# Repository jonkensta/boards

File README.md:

# boards

KiCad PCB projects plus the tooling to scaffold, check, and export them.
Requires KiCad 10 (`kicad-cli` on `PATH`), GNU make, Python 3, bash, and `unzip`.
No KiCad Python bindings are used anywhere (see "Design" below).

## Layout

```
boards/<id>/            one KiCad project per board, any depth; files named after the leaf dir
                        (boards/blinky/blinky.kicad_pro, boards/chromatone/isolator/isolator.kicad_pro)
lib/                    shared symbols, footprints, 3D models (nickname `boards` in every project)
templates/board/        project template used by `make new`
jobsets/fab.kicad_jobset  the one definition of every fabrication export (GUI and CLI)
boardtools/             Python helpers: s-expr parser, board facts, JLCPCB conversion, Specctra
                        DSN/SES, and the schematic/board generators (schgen, pcbgen) used by
                        boards/*/generate/
scripts/                scaffolder, smoke test, Freerouting autorouter (route.py)
boards/<id>/out/        generated outputs (git-ignored)
.github/workflows/      CI: unit tests, smoke test, ERC/DRC, fab exports in kicad/kicad:10.0
```

## Boards

| Board | What | Status (2026-09-19) |
| --- | --- | --- |
| [`chromatone/isolator`](boards/chromatone/isolator/README.md) | ISO7720 isolated SPI daughterboard, Pi (3.3 V) -> SK9822 strip (5 V), 46 x 30 mm | Rev A layout done, review-clean; pick passives in JLCPCB's BOM tool, then orderable |
| [`chromatone/dac`](boards/chromatone/dac/README.md) | PCM5102A I2S line-out DAC (experiment), 56 x 36 mm | Rev A layout done, review-clean, fully numbered BOM; not yet built |
| [`net/node`](boards/net/node/README.md) | RP2040 sensor-net node with neighbour links, four corner LEDs and sensor build variants, 48 x 48 mm, 4 layers | Rev A layout done and reviewed; ready to order after the owner's GUI check and quote (see its Resume path); no firmware yet |

`boards/chromatone/README.md` holds the Chromatone-wide decisions, strip wiring, order and
bench checklists. Every board so far was generated from `generate/` scripts (see below) and
put through an adversarial Codex review loop before being called done.

## Usage

```sh
make new NAME=blinky        # scaffold boards/blinky (fresh UUIDs, 50×50 mm outline, lib tables wired to lib/)
make new NAME=proj/rev2     # nested ids work too: boards/proj/rev2/rev2.kicad_pro
kicad boards/blinky/blinky.kicad_pro

make check  BOARD=blinky    # off-grid lint + ERC + DRC (schematic parity, zones refilled); fails on errors (STRICT=1: also warnings)
make fab    BOARD=blinky    # check, then run jobsets/fab.kicad_jobset -> boards/blinky/out/
make jlcpcb BOARD=blinky    # fab, then JLCPCB-format BOM + CPL -> boards/blinky/out/jlcpcb/
make parts  BOARD=blinky    # after fab: check every LCSC number in the BOM against JLCPCB's catalog
make check                  # all boards
make fab                    # all boards
make route  BOARD=blinky    # autoroute a placed board with Freerouting -> boards/blinky/out/route/ (see below)
```

`make fab` produces, per board (paths below are inside `boards/<id>/out/`):

| Output | Path |
| --- | --- |
| ERC/DRC reports (gating violations, plus a separate warnings report) | `{erc,drc}.rpt`, `{erc,drc}-warnings.rpt` |
| Off-grid connection points (gating; see `boardtools offgrid`) | `offgrid.rpt` |
| Gerbers (all copper layers up to In30, paste, silk, mask, edge) + `.gbrjob` | `./` |
| Excellon drill (PTH/NPTH split) + Gerber X2 maps | `drill/` |
| Gerbers + drill zipped for fab upload (no drill maps) | `<leaf>-gerbers.zip` |
| Pick-and-place CSV (mm, drill origin, DNP excluded) | `<leaf>-all-pos.csv` |
| BOM CSV grouped by Value/Description/Footprint/MPN/Manufacturer/LCSC | `<leaf>-bom.csv` |
| Schematic PDF | `<leaf>-schematic.pdf` |
| STEP model | `<leaf>.step` |
| JLCPCB CPL + BOM (`make jlcpcb`) | `jlcpcb/` |

The same jobset runs from the KiCad project manager: Jobsets → open `jobsets/fab.kicad_jobset`
→ run. Change export settings there once and both GUI and CI follow.

Other targets: `make parts` (see boardtools below), `make export` (jobset without the Makefile checks), `make erc|drc`, `make test`
(boardtools unit tests), `make smoke` (scaffolds throwaway 2- and 8-layer boards in a temp dir
and runs the whole pipeline, including a deliberate DRC failure and an off-grid child-sheet item), `make list`,
`make clean`.

KiCad 10 **design variants** (per-symbol DNP/field overrides, used by `net/node`) are honoured
by `kicad-cli sch export bom --variant <name>` and `pcb export pos --variant <name>`; the
jobset and `make jlcpcb` export the default variant only (backlog item 9 in `CLAUDE.md`).

## boardtools

```sh
python3 -m boardtools layers boards/blinky/blinky.kicad_pcb   # F.Cu,In1.Cu,In2.Cu,B.Cu
python3 -m boardtools info   boards/blinky/blinky.kicad_pcb   # title block + layer count
python3 -m boardtools jlcpcb pos <kicad-pos.csv> <cpl.csv>
python3 -m boardtools jlcpcb bom <kicad-bom.csv> <jlc-bom.csv>   # warns on lines without LCSC
python3 -m boardtools parts <kicad-bom.csv> [--db PATH] [--boards N] [--strict]
python3 -m boardtools offgrid boards/blinky/blinky.kicad_sch [--grid 1.27]
```

`parts` (and `make parts`, which checks the BOM `make fab` left in `out/` and refuses if it
is missing or older than the schematics, project file or jobset) is a **manual pre-order check**, not part of CI, because it
needs the network and uses the undocumented search endpoint behind jlcpcb.com/parts (one
request per distinct LCSC number, four at a time), which JLCPCB may change without notice.
`--db PATH` queries a jlcparts-style SQLite snapshot offline instead. It prints one row per
BOM line with basic/preferred/extended, live stock, and any problems:

- error: LCSC number malformed, not found at JLCPCB, or lookup failed (network/HTTP).
  With `--db` a miss is only "not in snapshot": snapshots omit parts with fewer than 5 in
  stock, and one with far fewer than ~600k parts is flagged as partial.
- warning: no LCSC number (nothing marks a line as hand-assembled, so this may be deliberate),
  stock below or within 3x of Qty x `--boards` (default 5, summed per LCSC number), MPN differs
  from the catalog, chip size in the footprint (0402/0603/...) differs from the catalog package.
- the summary counts distinct extended parts, each of which costs JLCPCB's loading fee.

Exit 1 on errors (`--strict` or `make parts STRICT=1`: also warnings), 2 if every lookup
failed or `--db` is unusable. Extra options go through `PARTS_ARGS`, e.g. `make parts PARTS_ARGS='--boards 10'`.

`offgrid` lists every electrical connection point off the 1.27 mm grid (symbol pins computed
from the embedded library symbols with the instance's rotation/mirror/unit/body style, wire
and bus ends, bus entries, junctions, no-connects, labels, sheet pins) in the sheet and every
child sheet file, one line per item with the sheet file and the nearest grid point, and exits 1
if there are any. `erc/<id>` gates on it as well as on ERC (both always run, so every report is
fresh): KiCad's ERC only warns (`endpoint_off_grid`) and reports one pin per symbol. `Schematic.write()`
in schgen refuses to write an off-grid sheet.

## Generating boards from Python

`boardtools.schgen` and `boardtools.pcbgen` write native `.kicad_sch` / `.kicad_pcb` files from
short Python scripts using the stock symbol and footprint libraries. `boards/*/*/generate/`
show the pattern: place symbols on the 1.27 mm grid, draw wires (or local labels for big parts),
run ERC, export the netlist, place footprints, route with `N(ref, pin)` net lookups, pour, run
DRC with `--refill-zones --save-board`, render. No KiCad Python bindings are involved.
Regenerating replaces every UUID, so once a board is edited in the KiCad GUI the scripts become
history rather than the source. `CLAUDE.md` lists the format details that cost time to learn
(pin transforms, junctions, PWR_FLAG, 0.65 mm pitch fan-out, mirrored silk, keepouts).

## Autorouting (Freerouting)

For a board whose placement is done, `make route BOARD=<id>` autoroutes it with
[Freerouting](https://github.com/freerouting/freerouting) and DRCs the result:

```sh
make route BOARD=chromatone/isolator                     # keep existing tracks/vias, route the rest
make route BOARD=chromatone/isolator ROUTE_ARGS=--strip  # drop all tracks/vias first, route from scratch
PASSES=20 make route BOARD=...                           # cap Freerouting's passes (default 100)
```

It writes a **new** board, `boards/<id>/out/route/<leaf>.kicad_pcb` (next to copies of the
project, rules and schematic so parity DRC works there, plus the `.dsn`, `.ses`,
`freerouting.log` and `drc.rpt`), then runs the same strict DRC as `make check` with
`--save-board` so the copy has its zones filled. The source board is never touched: open the
routed copy in KiCad, review it, and copy it over `boards/<id>/<leaf>.kicad_pcb` by hand if you
keep it. The default output directory `out/route/` is the only thing the script ever deletes:
it checks that `out/` and `out/route/` are real directories, then removes and recreates
`out/route/`, so no planted symlink or hard link can redirect any write (including DRC's
report) onto a source file. `scripts/route.py -o DIR` takes a new or empty real directory
only, never clears it, and refuses one that contains the board or lies inside the board's
directory other than under `out/`. `make fab`/`make clean` delete `out/`, including this.

kicad-cli has no Specctra DSN export or SES import (only the pcbnew GUI and its SWIG bindings
do), so `boardtools/specctra.py` writes the DSN and reads the SES textually, and
`scripts/route.py` appends the session's new tracks and vias to a copy of the board.
Freerouting runs from the Docker image `ghcr.io/freerouting/freerouting:2.4.1` (the release
jar needs Java 25); set `FREEROUTING="java -jar /path/to/freerouting-2.4.1.jar"` to use a
local jar, `FREEROUTING_VERSION` to pick another image tag. It is not part of CI or smoke.

What goes into the DSN: copper layers, the Edge.Cuts outline (inner loops as cut-outs), every
pad with its real shape and rotation on either side (rect, roundrect, oval, circle; chamfered
pads as their rectangle; trapezoid and custom pads as a rectangle enclosing all their copper,
primitives and strokes included), SMD and THT, NPTH holes and slots (slot walls also get the
copper-to-edge clearance, as KiCad's DRC applies it),
rule-area keepouts on the board and inside footprints, copper pours as planes (zone holes as
windows), existing tracks and vias as protected wiring, and netclass track width / clearance /
via size from the `.kicad_pro` (patterns and explicit assignments; a net in several classes
takes each rule from the highest-priority class that sets it, as KiCad 10 does). Net, reference
and pin names that a DSN cannot carry (`"`, backslash, non-ASCII) get generated identifiers and
are mapped back on import. Not modelled: per-layer padstacks, blind/buried/micro vias, arcs
(existing ones go in as chords), `.kicad_dru` custom rules, length/differential-pair
constraints. Tracks get their netclass width, so give power nets a
netclass if they need to be wider than Default. The router knows nothing about analog
return paths or decoupling loops; route those by hand first and let it finish the rest.

Verified on `chromatone/isolator` and `chromatone/dac` with all routing stripped: 100 %
routed in 4 to 10 s, 0 DRC errors, 0 warnings, 0 unconnected, 0 parity issues. Also clean:
the isolator with R1 (30 deg) and U1 (90 deg) moved to the back, and with a quoted net name
and a hole in a ground pour.

## Review workflow

Tooling changes and boards are reviewed adversarially with the Codex CLI: one fresh
`codex exec -s read-only` review, then `codex exec resume --last` rounds after each fix until
it reports no substantive findings. Codex is asked to reproduce (run `make test`/`make smoke`,
scaffold boards, run DRC in a temp copy), not just read. The findings that changed the design
are summarised in `CLAUDE.md` under "Review history".

## Design

- **Exports live in the jobset, checks live in the Makefile.** KiCad jobsets are the native,
  declarative way to define outputs and `kicad-cli jobset run` executes them headlessly. The
  Makefile adds what jobsets cannot: a separate warnings report, `STRICT`, purging stale outputs,
  and a hard guarantee that ERC/DRC pass before anything is exported (inside a jobset, a failing
  job only stops its own destination, and only with `--stop-on-error`).
- **No KiCad Python bindings.** The SWIG `pcbnew` module is deprecated and removed in KiCad 11;
  the IPC API needs a running KiCad and cannot export before KiCad 11. `boardtools` therefore
  only parses files (s-expressions, JSON, CSV). Anything that must modify a design goes through
  `kicad-cli` or the jobset. The one exception is `scripts/route.py`, which appends
  autorouted tracks to a *copy* of a board, because kicad-cli cannot import a Specctra session.
- **Template rules are conservative** (0.15 mm track/clearance, 0.3 mm drill, 0.3 mm copper-to-edge).
  Tighten or loosen per board in Board Setup → Constraints to match the fab.

## Conventions

- Put `MPN`, `Manufacturer`, and (for JLCPCB assembly) `LCSC` fields on symbols; the BOM export
  and JLCPCB conversion use them. Put ratings (dielectric, voltage, tolerance) in `Description`;
  it is exported and appended to the JLCPCB Comment.
- Custom parts go in `lib/`; stock KiCad library parts are referenced as usual.
- The template sets the drill/place origin at the outline's bottom-left corner; move it if you
  move the outline. Gerbers, drill, and position files use it.
- Board revision lives in the schematic title block.
- JLCPCB rotations are passed through unchanged; check the placement preview on the order page.
- Mounting holes get copper keepouts (`Board.keepout`) and nylon standoffs; on isolated boards
  metal hardware would tie the domains together.
- Passive references go on `F.Fab` (hidden); silk carries connector pin labels and test-point
  names instead.

## Where things stand

- Tooling is complete for the current workflow: scaffold, check, export, JLCPCB files, CI.
- Optional Freerouting autorouting (`make route`), outside CI.
- Backlog, ranked, lives in `CLAUDE.md` ("Ideas not yet implemented"): order bundle with a
  manifest, BOM/CPL lint (catalog side done: `make parts`), per-fab constraint profiles, HTML BOM, assembly drawings and revision
  diffs, panelization, revision in PCB markings, hierarchical sheets in `schgen`, per-variant
  jobset outputs, autorouter follow-ups.
- Known gap: `pcbgen` does not yet carry a schematic DNP flag onto footprints (parity DRC only
  warns about it).

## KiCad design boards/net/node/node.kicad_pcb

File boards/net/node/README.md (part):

# net/node

One cell of a sensor "net": a small RP2040 board with four corner RGB LEDs, a sensor and four
neighbour links. A node that detects something lights up and tells its neighbours; they
repeat the excitation one level weaker, so a wave ripples outwards and dies away. Any number
of nodes are tiled and cabled edge to edge (grid, hexagonal patch, irregular drape over a bush).

## Status: rev A ready to order pending the owner's GUI look and quote; reviewed (2026-09-25)

**Where it stands (2026-09-25, commit b260c7f):** every layout change of 2026-09-24/25 passed a
reproduction-based Codex review to NO SUBSTANTIVE FINDINGS (floorplan and J5 removal, crystal
isolation, corner LEDs and the pre-order fixes). A three-model pre-order panel (Codex, Kimi K3,
Gemini; Gemini weighted 1/4 at the owner's request) ran on 5175f76: Codex found the missing
BOOT 1 k (confirmed against the RP2040 hardware design guide p.9), hot-plug overvoltage, USB
backfeed and a piezo DC drive mode; Kimi's XSHUT claim was wrong (pads reset pulled down,
datasheet table 341). All accepted findings are fixed in b260c7f. What remains is in Resume path
items 4..7: the owner's GUI / 1:1 paper check, the quote, a small first batch, loose parts and cables.

2026-09-25: the single LED D2 (and the DNP D4) became **four WS2812B-2020-V6, one per corner** (D1..D4,
chained NE -> NW -> SW -> SE), run from +5V through a 5 V buffer U5 instead of the old D1 drop diode; the
panel's pre-order findings went in at the same time (BOOT 1 k R19, TVS D5, USB backfeed Schottky D6, balanced
quiet piezo drive, J1..J4 / SW1 out of the placement file, no vias in the J6 pogo pads). Board still 48 x 48.
`make check` 0 / 0 / 0 and no warnings, `make parts` 25 lines 0 / 0. See the Decisions entries dated
2026-09-25. The earlier status follows.

Rev A schematic is generated and ERC-clean. `generate/pcb.py` places and routes the whole
board (48 x 48 mm, 4 layers); `make check BOARD=net/node` passes with 0 violations,
0 unconnected items, 0 schematic-parity issues and no warnings. On 2026-09-24 the board was
re-placed and re-routed to the floorplan rule in Decisions: the RP2040 and its immediate
support fill the centre square between the four link housings, the peripherals take the
corners, and no pad, via, part or courtyard comes within 3.7 mm of a mounting-hole centre.
The sensor header J5 was removed in the same pass (see Decisions, sensor variants). The side-entry
connectors, their tiling alignment and the earlier review fixes are unchanged; the new layout has
not been reviewed yet (see Resume path). **No firmware, nothing ordered, no jig built.** LCSC
numbers verified 2026-09-24 via `make parts` (see Parts and cost). Next: review,
`make jlcpcb BOARD=net/node`, order-page check, jig.

## Concept and first-iteration scope

- The original idea: a cheap board with a bright LED, connected to four others, those to four
  more, forming a net that can be laid over an object, a wall or a bush. Each board has a sensor;
  on detection it lights up and signals its neighbours, who act on it with the signal
  attenuated at each hop.
- The behaviour is a cellular automaton: node state depends only on its own sensor and its
  immediate neighbours. That fact drove every interconnect decision below.
- First iteration is a **proof of concept**: indoor, no outdoor-proofing (no ESD/TVS on the
  links, no sealed connectors, no conformal coat), a **proximity** sensor first, and **per-node
  cost is the priority** because there may be many nodes. The vibration switch for a bush is
  kept as a build variant so the same PCB serves both.

## Decisions

- **Point-to-point neighbour links, not a bus.** The behaviour is local, so the cable topology
  *is* the logic topology: no addressing, no termination, no row/column config, any shape
  (irregular patches, 3- or 6-neighbour nodes, a cut net still works). The port a message
  arrives on gives direction for free (waves, flow away from source). A dead node is a hole the
  wave flows around. Rejected: CAN per row and column (two controllers and transceivers per
  node, termination at every row/column end, forces a rectangular grid, needs position config;
  contention was never the issue, a 20-node row at 500 kbit/s is idle), RS-485 (same problems),
  wireless / ESP-NOW / BLE mesh (removes data wires but not power, and adjacency from RSSI is
  unreliable; only worth it with battery nodes and much smaller LEDs).
- **Link = 5 V, DATA, GND on a keyed JST-XH 3-pin** (J1..J4 = N, E, S, W), straight cable, no
  crossover. DATA is a single-wire half-duplex UART: the GPIO is driven open-drain in firmware
  (drive low, else input), 4k7 pull-up to 3.3 V on every node (two nodes on a link give an
  effective 2.35 k), 100 R in series as cheap protection against a mis-configured push-pull
  pin. Four links on GPIO0..3 so one PIO block can run all four UARTs. Because every node shares
  the 5 V rail, there is no "one end unpowered" case to worry about on the data line. A keyed
  connector matters: a reversed 3-pin cable would put 5 V on either the data pin or the ground.
- **Side-entry link connectors** (2026-09-24): J1..J4 changed from the vertical B3B-XH-A
  (C144394) to the right-angle **S3B-XH-A(LF)(SN), LCSC C157928** (extended, ~142k in stock),
  so cables leave in the plane of the board and a node lies flat instead of standing on four
  upright plugs. Each housing sits on its own edge with the mouth facing out and **1.1 mm past
  the edge** (pin row 8.1 mm in). The housing is 11.5 mm deep (mouth 9.2 mm in front of the
  pins); flush mounting would cost another 1.1 mm of board on every side, and a bigger
  overhang leaves less of the 7 mm base on the board (at 1.1 mm about 6 mm is supported).
  Tiled nodes need at least 2.2 mm between boards plus the plug and cable bend. Footprint:
  `boards:JST_XH_S3B-XH-A_1x03_P2.50mm_Horizontal_EdgeMount`, the stock Connector_JST footprint
  with the silkscreen stopped 1.5 mm short of the mouth and the contact-slot marks removed.
  The stock silk crosses the board edge (`silk_edge_clearance` warnings), and trimming it in
  the generator instead gives `lib_footprint_mismatch` warnings. A through-hole footprint cannot be
  mirrored, so **pin 1 is now the counter-clockwise-first pin** of each edge (it was the
  clockwise-first pin with the vertical part). The pinout per connector is unchanged, and
  that is all a straight cable needs.
- **Tiling alignment** (2026-09-24): nodes are tiled by translation (every node the same way
  up), so each W connector J4 lines up exactly with the E connector J2 of its western neighbour
  and each S connector J3 with the N connector J1 of its southern neighbour. All four are also
  centred on their edges: pin 2 of J1/J3 at x 24.0 and of J2/J4 at y 24.0 (the board centre
  lines). `generate/pcb.py` derives the positions from two shared constants (W/2, H/2) and
  asserts both the alignment and the centring (1 um), so neither can silently regress. The pin
  rows coincide as sets, but because the footprint cannot be mirrored the pin numbers run the
  opposite way on facing edges: J2 (E) pin 1 is the south pin, J4 (W) pin 1 the north pin; J1
  (N) pin 1 is the east pin, J3 (S) pin 1 the west pin. A pin-1-to-pin-1 JST cable between two
  facing connectors therefore takes a half twist, which a loose cable does without complaint.
- **0402 caps at U1 pins 43..45** (2026-09-24): C10 (100 nF, ADC_AVDD), C11 (1 uF, VREG_VIN),
  C13 (1 uF, VREG_VOUT) and C15 (100 nF, DVDD) are 0402; every other passive stays 0603. The
  centred J4's courtyard starts 1.42 mm below U1's, less than a 0603 courtyard (1.46 mm), and
  the old 0603 column west of pins 43..45 sat exactly where J4 now is. In 0402 all four fit
  around U1's bottom-left corner with 1.4 to 2.9 mm of track from pin to pad (before: 2.6 to
  8.0 mm). Parts are JLCPCB basic: 100 nF Samsung CL05B104KB54PNC X7R 50 V (C307331) and 1 uF
  Samsung CL05A105KA5NQNC X5R 25 V (C52923; no basic 0402 1 uF is rated 50 V, and the rails
  are 3.3 V and 1.1 V). Their Descriptions end in "0402" so the BOM keeps them on separate lines.
- **Floorplan: MCU in the centre, peripherals in the corners, 3.7 mm hole clearance**
  (2026-09-24). The RP2040 and its immediate support (a cap at every supply pin, crystal,
  flash, LDO, USB series resistors) sit in the 26 mm centre square between the link housings,
  where the space is; each peripheral takes a corner, around its M2 hole, on the side where its
  pins leave U1 (rot 180): piezo BZ1 NE (driven from GPIO18/19 on U1's west edge since 2026-09-25, see
  crystal isolation), ToF U3 SE below J2
  (I2C / INT / XSHUT come off U1's east edge and cross the QSPI rows in one short B.Cu hop), pogo
  pads J6 SW (USB and, via the flash, BOOT leave U1's south edge; SWD comes down the west side),
  vibration switch SW1 NW (it needs only SENS_INT, one slow B.Cu lane under J1). The LEDs sat NE of
  U1 beside the crystal until 2026-09-25; they are now one per corner (see corner LEDs).
  **Hole clearance:** no copper pad, via, part body or courtyard within 3.7 mm of a hole
  centre, so a 5 mm M2 washer keeps more than 1.2 mm from every pad (before: C2's pad was
  3.08 mm from H1). Enforced twice. DRC: each hole gets a keepout annulus 2.6..3.7 mm
  (`pads`, `vias` and `footprints` not allowed; circumscribed polygon) besides the old 3.2 mm
  track keepout; the hole's own footprint (courtyard r 2.45) lies inside the annulus's hole, so
  the NPTH does not trip it. Verified on a copy: a cap pad and the piezo courtyard nudged into the
  annulus are both flagged, the holes are not. Generator: `pcb.py` asserts the pad-edge and
  courtyard distances from every hole centre (closest now: BZ1 courtyard 3.75 mm, pad J6.1
  6.43 mm).
- **Crystal isolation (2026-09-25).** An audit found switching copper beside the 12 MHz crystal
  nets (XIN, XOUT, the R1-Y1 node): BUZZ_B 0.51 mm, BUZZ_A 1.25 mm, +3V3 0.20 mm, DVDD 0.60 mm,
  SWCLK 1.0 mm, LINK_N 0.93 mm. Root cause: the piezo was on GPIO12/13 (pins 15/16), four pins
  from XIN/XOUT on the same package edge. Rule now: every non-GND net keeps >= 1.0 mm (same layer,
  edge to edge, tracks and pads) from crystal-net copper, the LED nets (LED_VDD, LED_DIN,
  D2 DOUT) and every D4 pad >= 2.0 mm; only the RP2040's own 0.4 mm-pitch pin field plus 1.5 mm
  of escape is exempt. `generate/xtal_check.py` measures it and `pcb.py` asserts it (checked: a
  LINK_N row nudged 0.4 mm and D4 moved 0.3 mm west each fail generation). Changes: the piezo
  moved to GPIO18/19 (pins 29/30, PWM slice 1, U1's NW corner; the only free even/odd pairs on
  the NE side are GPIO14/15 next to XIN, and GPIO8/9 whose escape collides with IOVDD 10's via,
  see the GPIO map) and reaches BZ1 on B.Cu under U1; XOUT follows XIN diagonally before turning
  north so IOVDD 22 / DVDD 23 / C5 stay >= 1 mm away (Y1 / R1 0.65 / 0.8 mm east, C2 vertical,
  C1 lower, LINK_N re-routed north of C2, D2 / D4 0.6 mm east); a F.Cu GND guard pour (priority 1,
  solid onto GND pads) covers the cluster. Its outline (`GUARD` in pcb.py: 24.12..31.5 x
  10.75..19.45, notched around R7 and D4) encloses nothing but GND and crystal copper, asserted
  with >= 0.2 mm from the outline to any other copper (checked: the old rectangle fails on D4's
  pads, LED_VDD and LINK_N). 19 GND vias, placed by script, stitch it to In1, 18 along its edge at
  <= 2 mm pitch except beside R1's XOUT pad (3.7), at C2's node pad (3.0 / 2.2) and at the U1
  escape (2.6); every one of the pour's three fill pieces has its own vias, and the load caps'
  and Y1's GND pads have short vias. In1 stays unbroken under the cluster (no other-net via
  inside the pour; In1 / In2 carry no tracks). The checker measures tracks (arcs included),
  vias, pads and zone copper, and raises on copper it does not model; D4's pads get the 2 mm
  rule whatever their net (GND included). **Known exemption:** within the RP2040's pad field plus
  1.5 mm, where the pins are 0.4 mm apart, the IOVDD 22 escape runs 0.20 mm and the DVDD 23
  escape 0.60 mm from XOUT's escape (SWCLK 1.0 mm). Pins 21 / 22 / 23 are adjacent, and 22 / 23
  are held in the NW fan's order by SWCLK / SWDIO / RUN, so no cheap re-route reaches 1 mm.
  Beyond that zone they are 1.07 mm (+3V3) and 1.51 mm (DVDD). Since the corner LEDs (2026-09-25) the
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
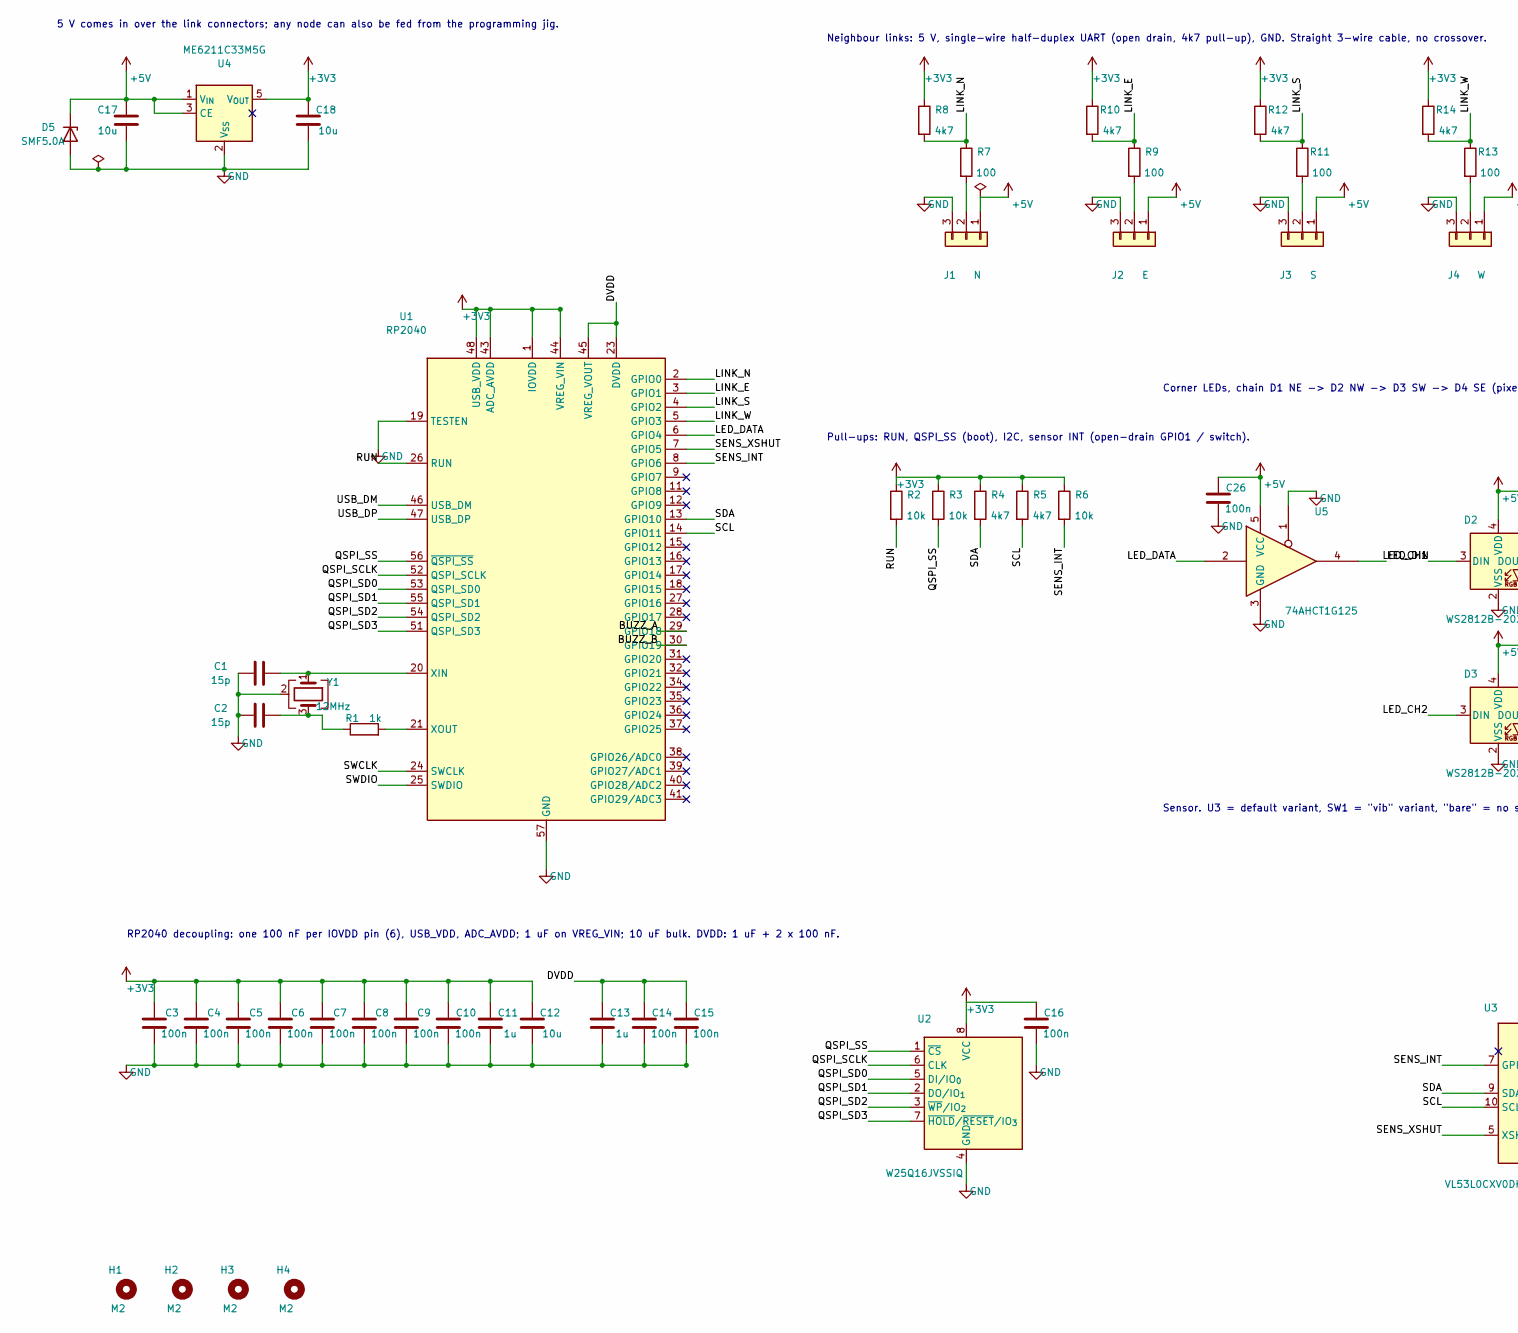
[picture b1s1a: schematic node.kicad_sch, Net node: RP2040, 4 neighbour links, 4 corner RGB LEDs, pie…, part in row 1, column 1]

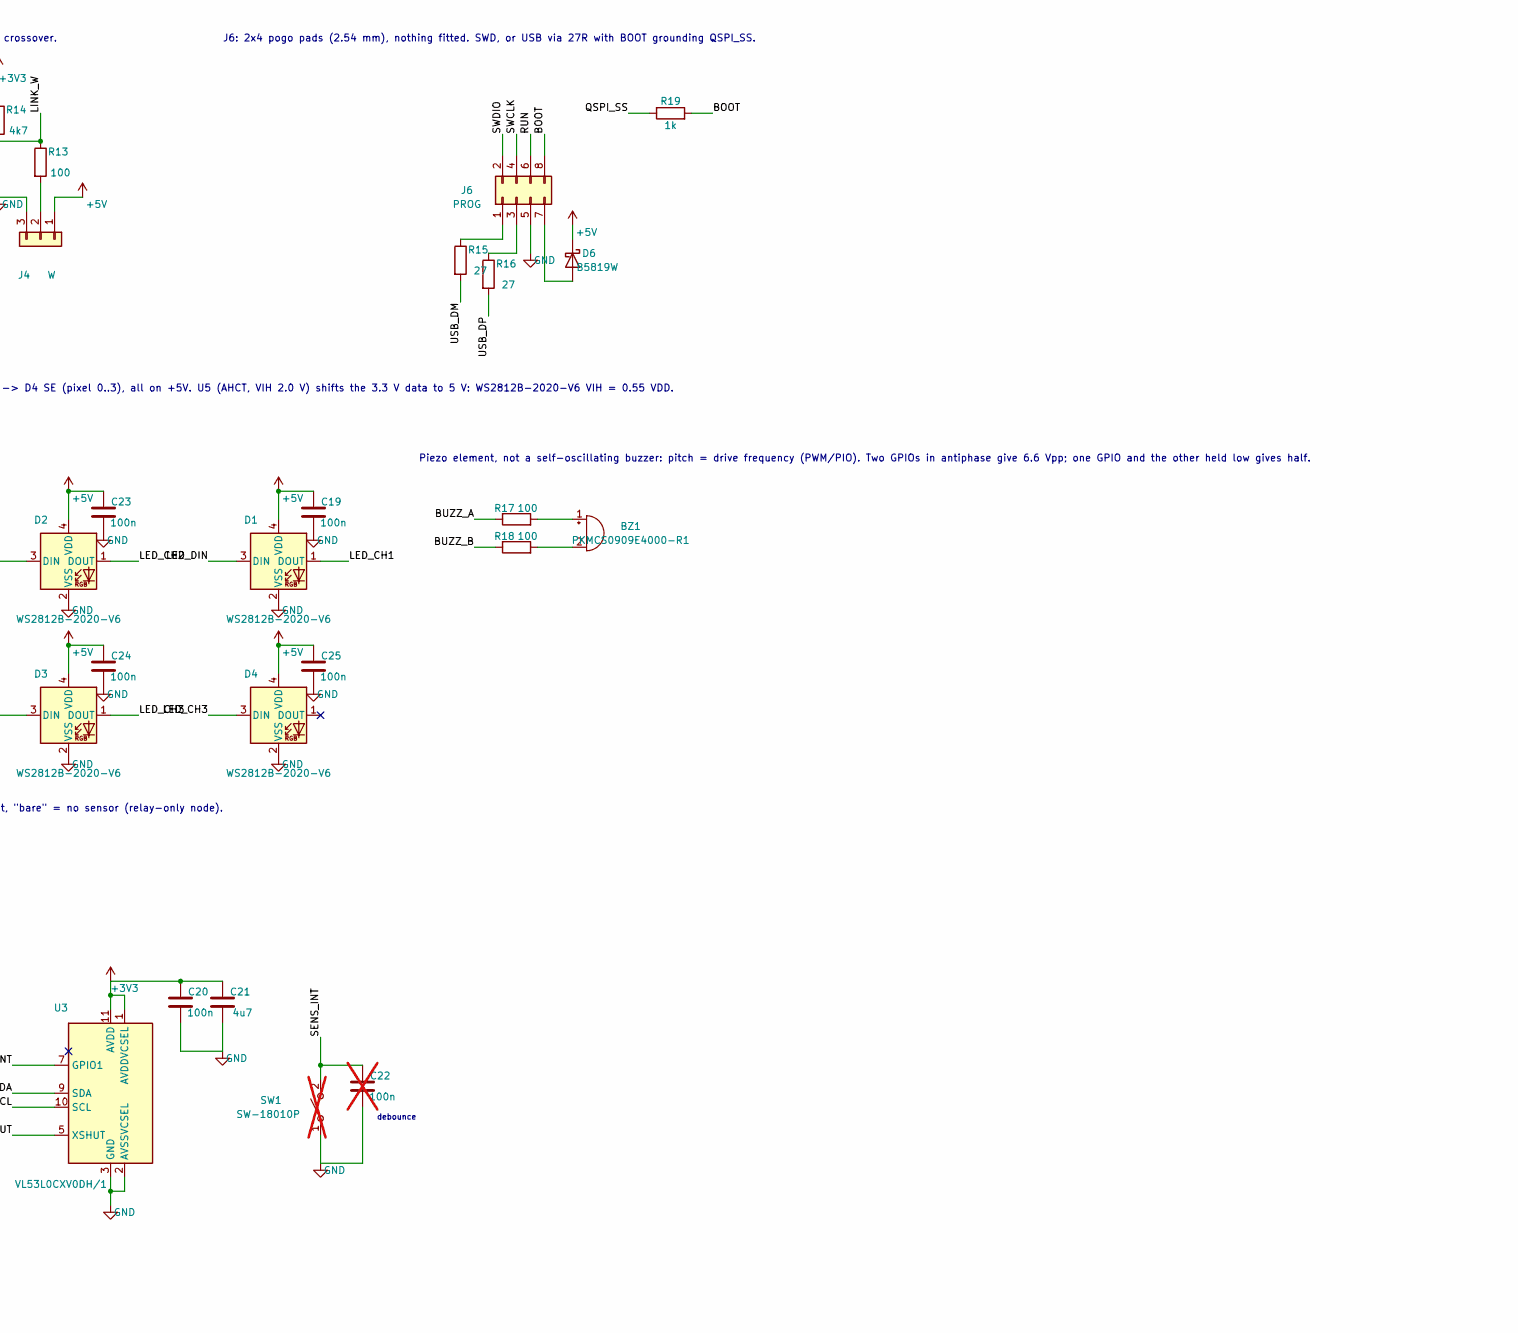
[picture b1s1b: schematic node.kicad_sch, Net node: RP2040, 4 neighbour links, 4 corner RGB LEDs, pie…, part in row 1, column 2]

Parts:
BZ1: PKMCS0909E4000-R1; Buzzer_Murata_PKMCS0909E; MPN PKMCS0909E4000-R1; LCSC C910763
C1, C2: 15p; C_0603_1608Metric; MPN CL10C150JB8NNNC; LCSC C1644
C3, C4, C5, C6, C7, C8, C9, C14, C16, C20: 100n; C_0603_1608Metric; MPN CC0603KRX7R9BB104; LCSC C14663
C10, C15, C19, C23, C24, C25, C26: 100n; C_0402_1005Metric; MPN CL05B104KB54PNC; LCSC C307331
C11, C13: 1u; C_0402_1005Metric; MPN CL05A105KA5NQNC; LCSC C52923
C12, C17, C18: 10u; C_0603_1608Metric; MPN CL10A106MA8NRNC; LCSC C96446
C21: 4u7; C_0603_1608Metric; MPN CL10A475KO8NNNC; LCSC C19666
C22: 100n; C_0603_1608Metric; MPN CC0603KRX7R9BB104; LCSC C14663; not fitted
D1, D2, D3, D4: WS2812B-2020-V6; LED_WS2812B-2020_PLCC4_2.0x2.0mm; MPN WS2812B-2020-V6; LCSC C52917434
D5: SMF5.0A; D_SOD-123F; MPN SMF5.0A; LCSC C193402
D6: B5819W; D_SOD-123; MPN B5819W SL; LCSC C8598
H1, H2, H3, H4: M2; MountingHole_2.2mm_M2
J1: N; JST_XH_S3B-XH-A_1x03_P2.50mm_Horizontal_EdgeMount; MPN S3B-XH-A(LF)(SN); LCSC C157928
J2: E; JST_XH_S3B-XH-A_1x03_P2.50mm_Horizontal_EdgeMount; MPN S3B-XH-A(LF)(SN); LCSC C157928
J3: S; JST_XH_S3B-XH-A_1x03_P2.50mm_Horizontal_EdgeMount; MPN S3B-XH-A(LF)(SN); LCSC C157928
J4: W; JST_XH_S3B-XH-A_1x03_P2.50mm_Horizontal_EdgeMount; MPN S3B-XH-A(LF)(SN); LCSC C157928
J6: PROG; PogoPads_2x04_P2.54mm
R1, R19: 1k; R_0603_1608Metric; MPN 0603WAF1001T5E; LCSC C21190
R2, R3, R6: 10k; R_0603_1608Metric; MPN 0603WAF1002T5E; LCSC C25804
R4, R5, R8, R10, R12, R14: 4k7; R_0603_1608Metric; MPN 0603WAF4701T5E; LCSC C23162
R7, R9, R11, R13, R17, R18: 100; R_0603_1608Metric; MPN 0603WAF1000T5E; LCSC C22775
R15, R16: 27; R_0603_1608Metric; MPN 0603WAF270JT5E; LCSC C25190
SW1: SW-18010P; MPN SW-18010P; LCSC C2681585; not fitted
U1: RP2040; QFN-56-1EP_7x7mm_P0.4mm_EP3.2x3.2mm; MPN RP2040; LCSC C2040
U2: W25Q16JVSSIQ; SOIC-8_5.3x5.3mm_P1.27mm; MPN W25Q16JVSSIQ; LCSC C82317
U3: VL53L0CXV0DH/1; ST_VL53L0X; MPN VL53L0CXV0DH/1; LCSC C91199
U4: ME6211C33M5G; SOT-23-5; MPN ME6211C33M5G-N; LCSC C82942
U5: 74AHCT1G125; SOT-23-5; MPN SN74AHCT1G125DBVR; LCSC C7484
Y1: 12MHz; Crystal_SMD_3225-4Pin_3.2x2.5mm; MPN ABM8-272-T3; LCSC C20625731

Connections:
+3V3: C3.1, C4.1, C5.1, C6.1, C7.1, C8.1, C9.1, C10.1, C11.1, C12.1, C16.1, C18.1, C20.1, C21.1, R2.1, R3.1, R4.1, R5.1, R6.1, R8.1, R10.1, R12.1, R14.1, U1.1 (IOVDD), U1.10 (IOVDD), U1.22 (IOVDD), U1.33 (IOVDD), U1.42 (IOVDD), U1.43 (ADC_AVDD), U1.44 (VREG_VIN), U1.48 (USB_VDD), U1.49 (IOVDD), U2.8 (VCC), U3.1 (AVDDVCSEL), U3.11 (AVDD), U4.5 (V_{OUT})
+5V: C17.1, C19.1, C23.1, C24.1, C25.1, C26.1, D1.4 (VDD), D2.4 (VDD), D3.4 (VDD), D4.4 (VDD), D5.1 (K), D6.1 (K), J1.1, J2.1, J3.1, J4.1, U4.1 (V_{IN}), U4.3 (CE), U5.5 (VCC)
/BOOT: J6.8, R19.2
/BUZZ_A: R17.1, U1.29 (GPIO18)
/BUZZ_B: R18.1, U1.30 (GPIO19)
/DVDD: C13.1, C14.1, C15.1, U1.23 (DVDD), U1.45 (VREG_VOUT), U1.50 (DVDD)
/LED_CH1: D1.1 (DOUT), D2.3 (DIN)
/LED_CH2: D2.1 (DOUT), D3.3 (DIN)
/LED_CH3: D3.1 (DOUT), D4.3 (DIN)
/LED_DATA: U1.6 (GPIO4), U5.2
/LED_DIN: D1.3 (DIN), U5.4
/LINK_E: R9.1, R10.2, U1.3 (GPIO1)
/LINK_N: R7.1, R8.2, U1.2 (GPIO0)
/LINK_S: R11.1, R12.2, U1.4 (GPIO2)
/LINK_W: R13.1, R14.2, U1.5 (GPIO3)
/QSPI_SCLK: U1.52 (QSPI_SCLK), U2.6 (CLK)
/QSPI_SD0: U1.53 (QSPI_SD0), U2.5 (DI/IO_{0})
/QSPI_SD1: U1.55 (QSPI_SD1), U2.2 (DO/IO_{1})
/QSPI_SD2: U1.54 (QSPI_SD2), U2.3 (~WP/IO_{2})
/QSPI_SD3: U1.51 (QSPI_SD3), U2.7 (~HOLD/~RESET/IO_{3})
/QSPI_SS: R3.2, R19.1, U1.56 (~QSPI_SS), U2.1 (~CS)
/RUN: J6.6, R2.2, U1.26 (RUN)
/SCL: R5.2, U1.14 (GPIO11), U3.10 (SCL)
/SDA: R4.2, U1.13 (GPIO10), U3.9 (SDA)
/SENS_INT: C22.1, R6.2, SW1.2 (B), U1.8 (GPIO6), U3.7 (GPIO1)
/SENS_XSHUT: U1.7 (GPIO5), U3.5 (XSHUT)
/SWCLK: J6.4, U1.24 (SWCLK)
/SWDIO: J6.2, U1.25 (SWDIO)
/USB_DM: R15.2, U1.46 (USB_DM)
/USB_DP: R16.2, U1.47 (USB_DP)
GND: C1.1, C2.1, C3.2, C4.2, C5.2, C6.2, C7.2, C8.2, C9.2, C10.2, C11.2, C12.2, C13.2, C14.2, C15.2, C16.2, C17.2, C18.2, C19.2, C20.2, C21.2, C22.2, C23.2, C24.2, C25.2, C26.2, D1.2 (VSS), D2.2 (VSS), D3.2 (VSS), D4.2 (VSS), D5.2 (A), J1.3, J2.3, J3.3, J4.3, J6.5, SW1.1 (A), U1.19 (TESTEN), U1.57 (GND), U2.4 (GND), U3.2 (AVSSVCSEL), U3.3 (GND), U3.4 (GND), U3.6 (GND), U3.12 (GND), U4.2 (V_{SS}), U5.1, U5.3 (GND), Y1.2 (G), Y1.4 (G)
unnamed: BZ1.1 (+), R17.2
unnamed: BZ1.2 (-), R18.2
unnamed: C2.2, R1.1, Y1.3
unnamed: D6.2 (A), J6.7
unnamed: J1.2, R7.2
unnamed: J2.2, R9.2
unnamed: J3.2, R11.2
unnamed: J4.2, R13.2
unnamed: J6.1, R15.1
unnamed: J6.3, R16.1
unnamed: C1.2, U1.20 (XIN), Y1.1
unnamed: R1.2, U1.21 (XOUT)

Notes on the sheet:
RP2040 decoupling: one 100 nF per IOVDD pin (6), USB_VDD, ADC_AVDD; 1 uF on VREG_VIN; 10 uF bulk. DVDD: 1 uF + 2 x 100 nF.
Pull-ups: RUN, QSPI_SS (boot), I2C, sensor INT (open-drain GPIO1 / switch).
Neighbour links: 5 V, single-wire half-duplex UART (open drain, 4k7 pull-up), GND. Straight 3-wire cable, no crossover.
J6: 2x4 pogo pads (2.54 mm), nothing fitted. SWD, or USB via 27R with BOOT grounding QSPI_SS.
5 V comes in over the link connectors; any node can also be fed from the programming jig.
Corner LEDs, chain D1 NE -> D2 NW -> D3 SW -> D4 SE (pixel 0..3), all on +5V. U5 (AHCT, VIH 2.0 V) shifts the 3.3 V data to 5 V: WS2812B-2020-V6 VIH = 0.55 VDD.
Sensor. U3 = default variant, SW1 = "vib" variant, "bare" = no sensor (relay-only node).
debounce
Piezo element, not a self-oscillating buzzer: pitch = drive frequency (PWM/PIO). Two GPIOs in antiphase give 6.6 Vpp; one GPIO and the other held low gives half.

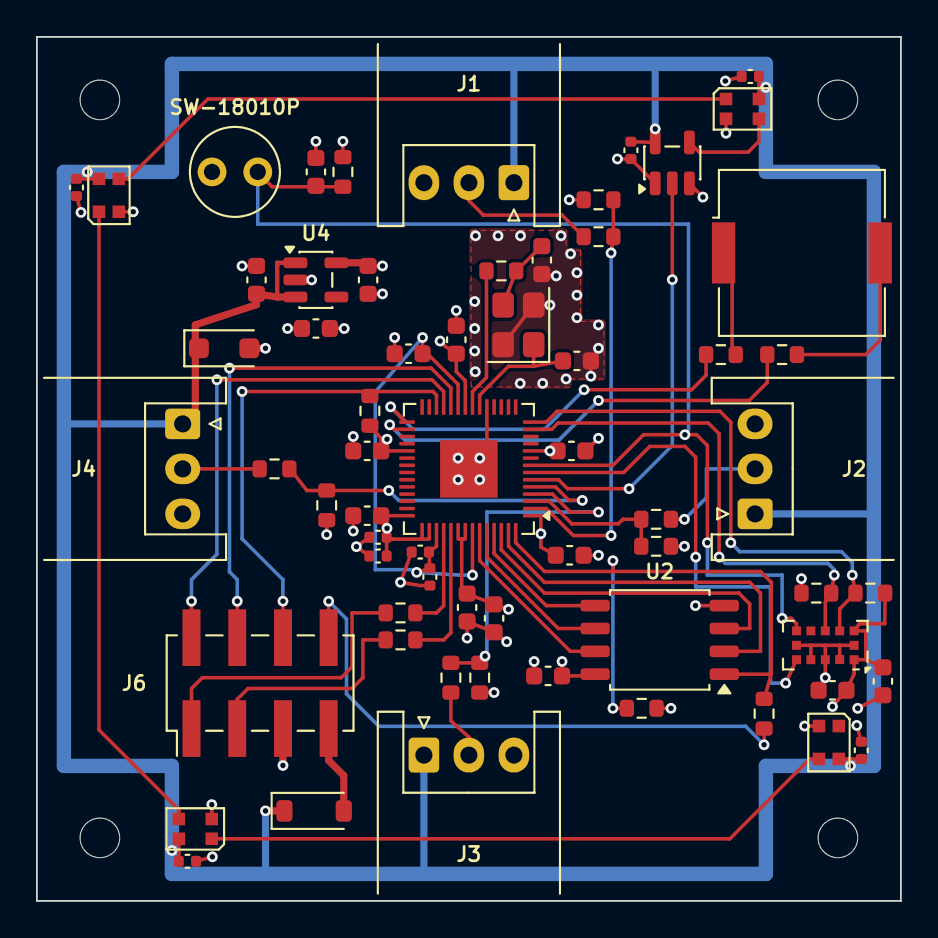
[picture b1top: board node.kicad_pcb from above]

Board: 4 copper layers, 48.0 x 48.0 mm, 68 parts (0 on the bottom side), 43 nets.

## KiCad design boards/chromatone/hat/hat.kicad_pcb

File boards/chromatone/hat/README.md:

# chromatone/hat

Raspberry Pi HAT that merges `chromatone/isolator` (ISO7720 isolated SPI -> SK9822 strip)
and `chromatone/dac` (PCM5102A I2S line out) onto one 65 x 56.5 mm board that plugs onto
the 40-pin header of a Pi 4B (or any 40-pin Pi; it overhangs a Zero 2 W). Both source
boards stay in the repo as history; this is the board to order.

## Status (2026-09-21)

- Schematic and PCB generated (`generate/`), ERC and DRC clean including schematic parity.
  Not yet ordered; the JLCPCB BOM step below still applies.
- Codex review (2026-09-21): no electrical or layout blocker. Ordering notes: D2 (blue LED),
  J1 (2x20 socket) and R1/R2 (47 R) have no LCSC number yet; J1 is the only back-side part and
  is THT, so either choose JLCPCB Standard assembly (both sides) or hand-solder the socket
  (Economic assembly is single-sided). Keep the 8.5 mm body height if substituting.
- Decisions taken: full HAT outline (holes 58 x 49 mm, socket on the back at the HAT-spec
  position: pin 1 at (8.37, 4.77) from the top-left corner, pins along the top edge); ID EEPROM
  footprints present but DNP; camera/display slots omitted (not used on the bike).
- Open question: with a Pi 4B in hand, try its onboard 3.5 mm jack into the speaker first. If
  it is good enough the DAC half (U2, U3, J3, C5..C16, R5..R11, D3, TP7..TP9) can be left
  unpopulated, and a rev B could drop it.

## Resume path

1. Decide the DAC question: plug the speaker into the Pi 4B's own 3.5 mm jack (PWM audio,
   about 11 effective bits, some hiss). Good enough -> order with U2, U3, J3, C5..C16, R5..R11,
   D3 unpopulated (add `dnp=True` to those `place()` calls in `generate/schematic.py`, regenerate
   schematic -> netlist -> `pcb.py`; pcbgen copies dnp into the footprints so the CPL/BOM follow).
2. In JLCPCB's BOM tool pick: 47 R 0603 (R1, R2), blue 0603 LED (D2), 2x20 female socket 8.5 mm
   (J1, THT, back side -> Standard assembly or hand-solder). Everything else has an LCSC number.
3. Check LED polarity and J2/J3 orientation in the placement preview; `make jlcpcb
   BOARD=chromatone/hat` writes `out/jlcpcb/`.
4. Bench: per `chromatone/README.md` (isolator LEDs, 8 MHz first, probe one domain at a time),
   `dtoverlay=hifiberry-dac` if the DAC is fitted, XSMT from GPIO5 optional.
5. If the layout is ever edited in the KiCad GUI, stop regenerating; `generate/` becomes history.

Design was built and reviewed on branch `worktree-chromatone-hat` (Codex, two rounds, no
electrical or layout finding); see CLAUDE.md for the pcbgen features it introduced.

## Pi pins used

| Signal | Pi pin | GPIO | Goes to |
| --- | --- | --- | --- |
| 3V3 | 1 (17) | | ISO7720 VCC1, EEPROM pull-ups |
| 5V | 2 (4) | | ME6211 LDO -> +3V3_DAC |
| SCLK | 23 | GPIO11 | ISO7720 INA -> strip CI |
| MOSI | 19 | GPIO10 | ISO7720 INB -> strip DI |
| BCK | 12 | GPIO18 | PCM5102A BCK (33 R) |
| LRCK | 35 | GPIO19 | PCM5102A LRCK (33 R) |
| DIN | 40 | GPIO21 | PCM5102A DIN (33 R) |
| XSMT | 29 | GPIO5 | PCM5102A XSMT (10k pull-up; GPIO5 defaults to pull-up, so un-muted until driven) |
| ID_SD/ID_SC | 27/28 | GPIO0/1 | 24LC32 (DNP) |
| GND | 6, 9, 14, ... | | GND (Pi domain only) |

The LED domain (+5V_LED, GND_LED, J2 to pixel 0) touches nothing on the Pi. Everything in
`chromatone/README.md` about strip wiring, the VDD2 tap at pixel 0, 8 MHz SPI and probing
one domain at a time still applies.

## Layout (rev A, 65 x 56.5 mm, 2 layers)

- Header along the top edge, socket on the back (the only back-side part). 5V and BCK leave
  their pads on the back (5V down the west side, BCK east under the socket); everything else
  escapes on the front. Pin 25 (GND) needs a stub and via because the BCK run isolates its
  pour sliver.
- DAC block: the `chromatone/dac` layout rotated 90 deg onto the right half, jack on the bottom
  edge at x = 53 (the right edge is out: the Pi's USB stack rises above the HAT there),
  PCM5102A at (48, 19.5), the 33 R I2S resistors in a row under the header, LDO at (37, 23.5).
- Isolator block: the `chromatone/isolator` layout rotated 180 deg into the bottom left. J2 on
  the left edge, U1 on a vertical 3 mm barrier at x = 23, LED island x < 21.5 / y > 31.5 with
  its own pour; hole H3 sits inside it (copper keepout; use a nylon standoff there).
- SPI feeds (MOSI, SCLK) run down the middle as columns at x = 32 / 34; 3V3 hops under them on
  the back and runs down x = 35.5. ID EEPROM (DNP) in the left-centre with ID_SD/ID_SC on the
  back under the columns.
- Test points: SCLK, MOSI, GND_A (Pi domain), CLK, DATA, GND_B (LED domain), LRCK, BCK, GND
  (DAC). Probe one domain at a time.
- Pi 4B PoE header sits under x 54..63, y 6..14; nothing on the back there.
- `generate/drc.sh` regenerates and prints DRC findings in board-local mm.

## Files

- `hat.kicad_pro` / `.kicad_sch` / `.kicad_pcb` — KiCad project
- `generate/` — schematic and board generators (see its README)
- `sym-lib-table` / `fp-lib-table` — project library tables pointing at the shared `lib/`

## Build

```sh
make check  BOARD=chromatone/hat
make fab    BOARD=chromatone/hat
make jlcpcb BOARD=chromatone/hat
```

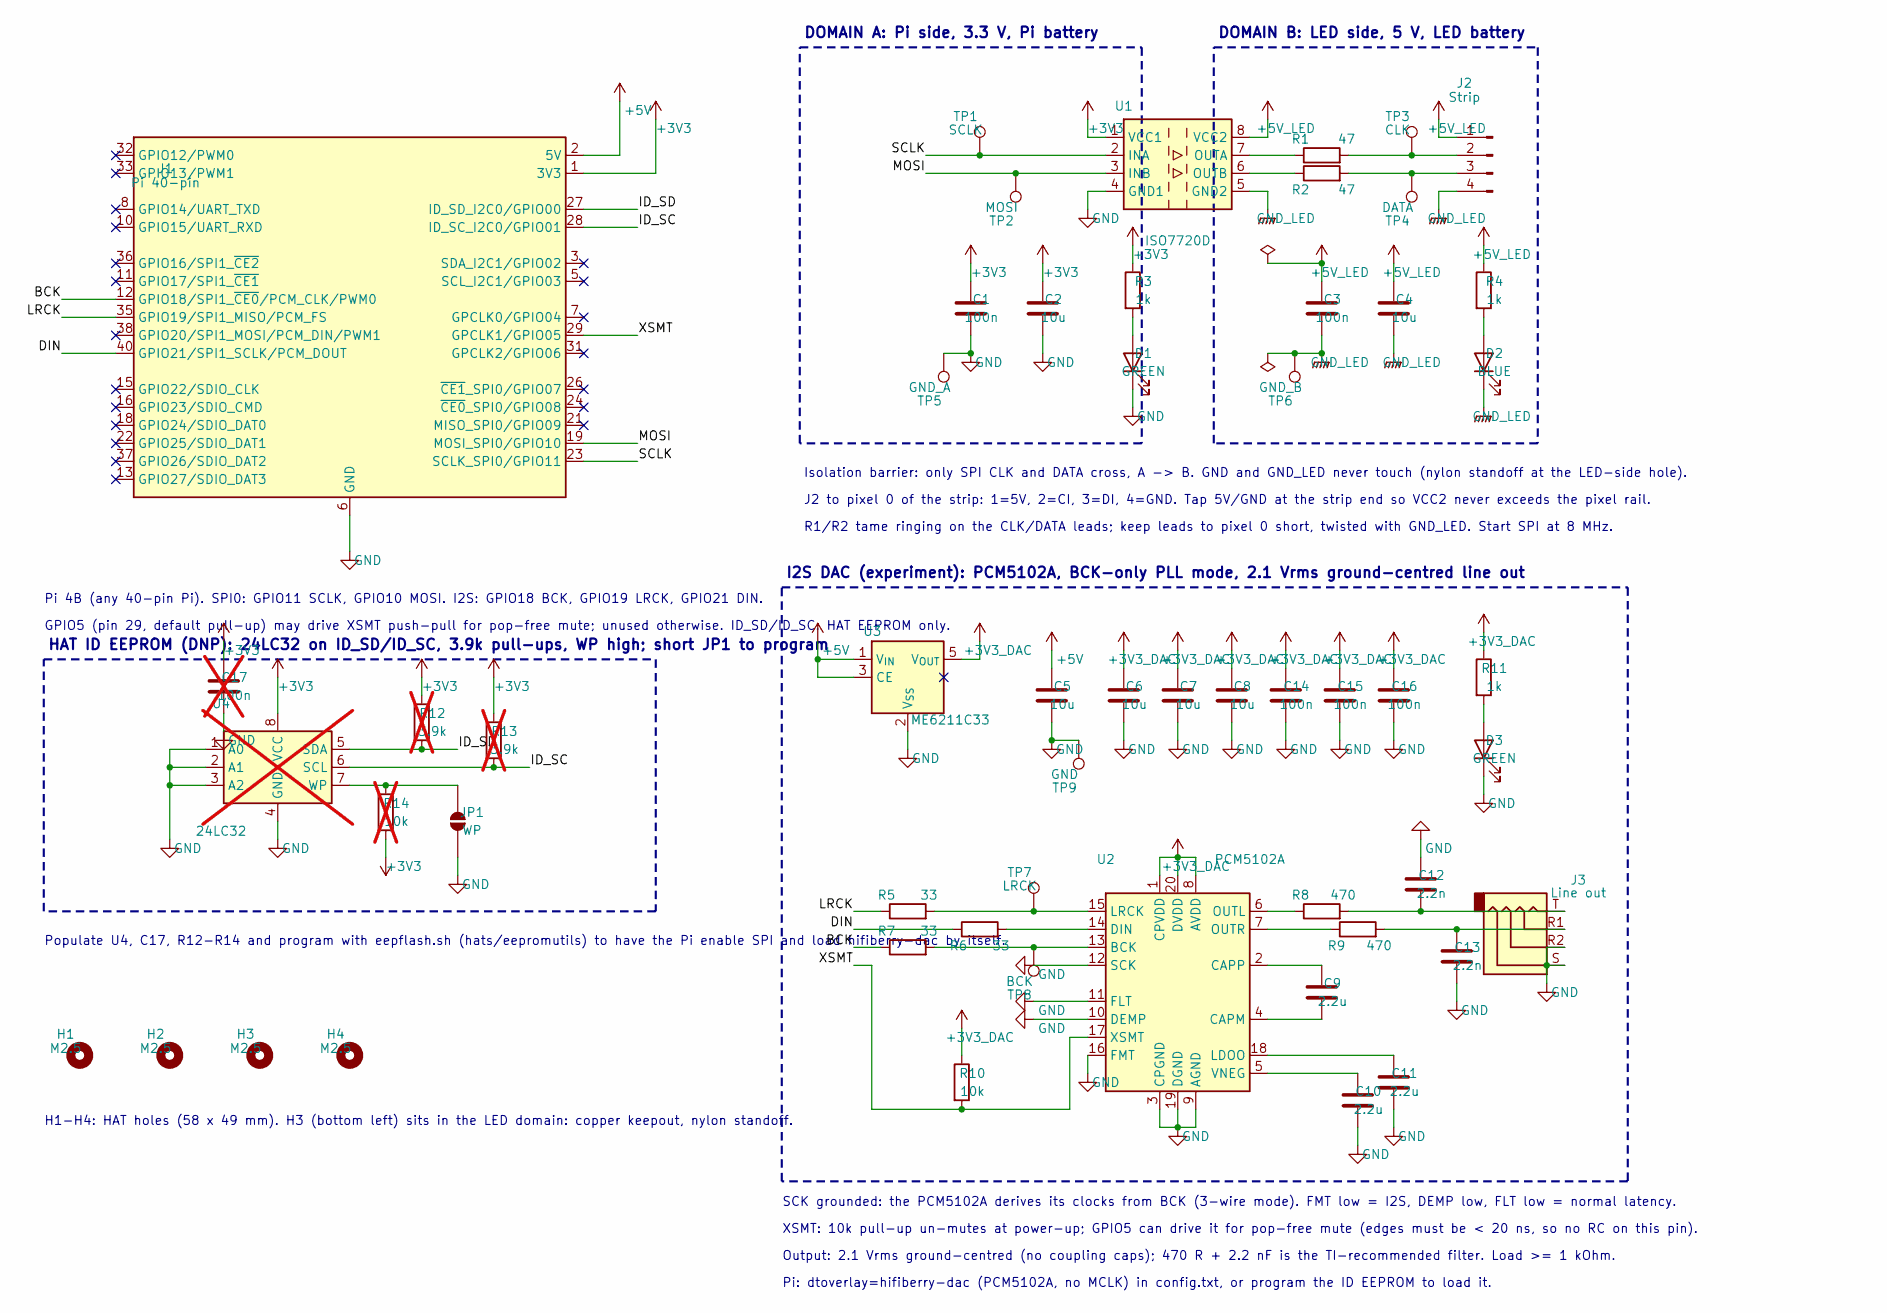
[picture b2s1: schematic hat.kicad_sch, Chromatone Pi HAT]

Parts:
C1, C3, C14, C15, C16: 100n; C_0603_1608Metric; MPN CC0603KRX7R9BB104; LCSC C14663
C2, C4, C5, C6, C7, C8: 10u; C_0603_1608Metric; MPN CL10A106MA8NRNC; LCSC C96446
C9, C10, C11: 2.2u; C_0603_1608Metric; MPN CL10A225KO8NNNC; LCSC C23630
C12, C13: 2.2n; C_0603_1608Metric; MPN 0603B222K500NT; LCSC C1604
C17: 100n; C_0603_1608Metric; MPN CC0603KRX7R9BB104; LCSC C14663; not fitted
D1, D3: GREEN; LED_0603_1608Metric; MPN 19-217/GHC-YR1S2/3T; LCSC C72043
D2: BLUE; LED_0603_1608Metric
H1, H2, H3, H4: M2.5; MountingHole_2.7mm_M2.5
J1: Pi 40-pin; PinSocket_2x20_P2.54mm_Vertical; MPN PPTC202LFBN-RC
J2: Strip; JST_XH_B4B-XH-A_1x04_P2.50mm_Vertical; MPN B4B-XH-A(LF)(SN); LCSC C144395
J3: Line out; Jack_3.5mm_PJ320D_Horizontal; MPN PJ-320D; LCSC C431535
JP1: WP; SolderJumper-2_P1.3mm_Open_RoundedPad1.0x1.5mm
R1, R2: 47; R_0603_1608Metric
R3, R4, R11: 1k; R_0603_1608Metric; MPN 0603WAF1001T5E; LCSC C21190
R5, R6, R7: 33; R_0603_1608Metric; MPN 0603WAF330JT5E; LCSC C23140
R8, R9: 470; R_0603_1608Metric; MPN 0603WAF4700T5E; LCSC C23179
R10: 10k; R_0603_1608Metric; MPN 0603WAF1002T5E; LCSC C25804
R12, R13: 3.9k; R_0603_1608Metric; not fitted
R14: 10k; R_0603_1608Metric; MPN 0603WAF1002T5E; LCSC C25804; not fitted
TP1: SCLK; TestPoint_Pad_D1.5mm
TP2: MOSI; TestPoint_Pad_D1.5mm
TP3: CLK; TestPoint_Pad_D1.5mm
TP4: DATA; TestPoint_Pad_D1.5mm
TP5: GND_A; TestPoint_Pad_D1.5mm
TP6: GND_B; TestPoint_Pad_D1.5mm
TP7: LRCK; TestPoint_Pad_D1.5mm
TP8: BCK; TestPoint_Pad_D1.5mm
TP9: GND; TestPoint_Pad_D1.5mm
U1: ISO7720D; SOIC-8_3.9x4.9mm_P1.27mm; MPN ISO7720DR; LCSC C486037
U2: PCM5102A; TSSOP-20_4.4x6.5mm_P0.65mm; MPN PCM5102APWR; LCSC C107671
U3: ME6211C33; SOT-23-5; MPN ME6211C33M5G-N; LCSC C82942
U4: 24LC32; SOIC-8_3.9x4.9mm_P1.27mm; MPN 24LC32AT-I/SN; not fitted

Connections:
+3V3: C1.1, C2.1, C17.1, J1.1 (3V3), J1.17 (3V3), R3.1, R12.1, R13.1, R14.2, U1.1 (VCC1), U4.8 (VCC)
+3V3_DAC: C6.1, C7.1, C8.1, C14.1, C15.1, C16.1, R10.1, R11.1, U2.1 (CPVDD), U2.8 (AVDD), U2.20 (DVDD), U3.5 (V_{OUT})
+5V: C5.1, J1.2 (5V), J1.4 (5V), U3.1 (V_{IN}), U3.3 (CE)
+5V_LED: C3.1, C4.1, J2.1, R4.1, U1.8 (VCC2)
/BCK: J1.12 (GPIO18/SPI1_~CE0/PCM_CLK/PWM0), R7.1
/DIN: J1.40 (GPIO21/SPI1_SCLK/PCM_DOUT), R6.1
/ID_SC: J1.28 (ID_SC_I2C0/GPIO01), R13.2, U4.6 (SCL)
/ID_SD: J1.27 (ID_SD_I2C0/GPIO00), R12.2, U4.5 (SDA)
/LRCK: J1.35 (GPIO19/SPI1_MISO/PCM_FS), R5.1
/MOSI: J1.19 (MOSI_SPI0/GPIO10), TP2.1, U1.3 (INB)
/SCLK: J1.23 (SCLK_SPI0/GPIO11), TP1.1, U1.2 (INA)
/XSMT: J1.29 (GPCLK1/GPIO05), R10.2, U2.17 (XSMT)
GND: C1.2, C2.2, C5.2, C6.2, C7.2, C8.2, C10.2, C11.2, C12.2, C13.2, C14.2, C15.2, C16.2, C17.2, D1.1 (K), D3.1 (K), J1.6 (GND), J1.9 (GND), J1.14 (GND), J1.20 (GND), J1.25 (GND), J1.30 (GND), J1.34 (GND), J1.39 (GND), J3.R2, J3.S, JP1.1 (A), TP5.1, TP9.1, U1.4 (GND1), U2.3 (CPGND), U2.9 (AGND), U2.10 (DEMP), U2.11 (FLT), U2.12 (SCK), U2.16 (FMT), U2.19 (DGND), U3.2 (V_{SS}), U4.1 (A0), U4.2 (A1), U4.3 (A2), U4.4 (GND)
GND_LED: C3.2, C4.2, D2.1 (K), J2.4, TP6.1, U1.5 (GND2)
unnamed: C12.1, J3.T, R8.2
unnamed: C13.1, J3.R1, R9.2
unnamed: D1.2 (A), R3.2
unnamed: D2.2 (A), R4.2
unnamed: D3.2 (A), R11.2
unnamed: J2.2, R1.2, TP3.1
unnamed: J2.3, R2.2, TP4.1
unnamed: JP1.2 (B), R14.1, U4.7 (WP)
unnamed: R1.1, U1.7 (OUTA)
unnamed: R2.1, U1.6 (OUTB)
unnamed: R7.2, TP8.1, U2.13 (BCK)
unnamed: C9.2, U2.4 (CAPM)
unnamed: C9.1, U2.2 (CAPP)
unnamed: R6.2, U2.14 (DIN)
unnamed: C11.1, U2.18 (LDOO)
unnamed: R5.2, TP7.1, U2.15 (LRCK)
unnamed: R8.1, U2.6 (OUTL)
unnamed: R9.1, U2.7 (OUTR)
unnamed: C10.1, U2.5 (VNEG)

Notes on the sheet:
Pi 4B (any 40-pin Pi). SPI0: GPIO11 SCLK, GPIO10 MOSI. I2S: GPIO18 BCK, GPIO19 LRCK, GPIO21 DIN.
GPIO5 (pin 29, default pull-up) may drive XSMT push-pull for pop-free mute; unused otherwise. ID_SD/ID_SC: HAT EEPROM only.
DOMAIN A: Pi side, 3.3 V, Pi battery
DOMAIN B: LED side, 5 V, LED battery
Isolation barrier: only SPI CLK and DATA cross, A -> B. GND and GND_LED never touch (nylon standoff at the LED-side hole).
J2 to pixel 0 of the strip: 1=5V, 2=CI, 3=DI, 4=GND. Tap 5V/GND at the strip end so VCC2 never exceeds the pixel rail.
R1/R2 tame ringing on the CLK/DATA leads; keep leads to pixel 0 short, twisted with GND_LED. Start SPI at 8 MHz.
I2S DAC (experiment): PCM5102A, BCK-only PLL mode, 2.1 Vrms ground-centred line out
SCK grounded: the PCM5102A derives its clocks from BCK (3-wire mode). FMT low = I2S, DEMP low, FLT low = normal latency.
XSMT: 10k pull-up un-mutes at power-up; GPIO5 can drive it for pop-free mute (edges must be < 20 ns, so no RC on this pin).
Output: 2.1 Vrms ground-centred (no coupling caps); 470 R + 2.2 nF is the TI-recommended filter. Load >= 1 kOhm.
Pi: dtoverlay=hifiberry-dac (PCM5102A, no MCLK) in config.txt, or program the ID EEPROM to load it.
HAT ID EEPROM (DNP): 24LC32 on ID_SD/ID_SC, 3.9k pull-ups, WP high; short JP1 to program
Populate U4, C17, R12-R14 and program with eepflash.sh (hats/eepromutils) to have the Pi enable SPI and load hifiberry-dac by itself.
H1-H4: HAT holes (58 x 49 mm). H3 (bottom left) sits in the LED domain: copper keepout, nylon standoff.
